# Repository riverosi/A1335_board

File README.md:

# A1335_board Project v1
Reposiorio de la pcb que usa el sensor [A1335](https://www.allegromicro.com/en/products/sense/linear-and-angular-position/angular-position-sensor-ics/a1335) de Allegro. Esta vesión tiene los siguientes requerimientos:
- [x] Los capacitores de desacople van a ir cerca del integrado
- [x] La mascara tendra una simbologia con la asigancion de pines
- [x] No se usaran las anotaciones en el cobre
- [x] Dimensiones propuestas: 50x40 mm
- [x] Se usaran pines como conectores
- [x] Tendrá 4 mountingholes tamaño M3
Vistas 3d del PCB:

# Montaje final del PCB con el Bumper:

## Firmware
En la carpeta firmware están los archivos `__angle_driver.h` y `__angle_driver.c`, que son los drivers en c para la plataforma de desarollo EDU-CIAA. En el main hay un ejemplo de como inicializar el dispositivo con las direcciones correspondientes al hardware que se desarrollo en la v1 (0x0C). 

## Software
Para desarrollar la placa se uso:
* [Doxygen](https://www.doxygen.nl/index.html) - To generate the documentation
* [VSCode](https://code.visualstudio.com/) - To communicate data through the UART (Developing)
* [KiCad](https://kicad.org/) - To develop de board

## Hardware
Para desarrollar la placa se uso **Kicad**, se debe de incluir la libraria HALL con el simbolo del componente A1335.

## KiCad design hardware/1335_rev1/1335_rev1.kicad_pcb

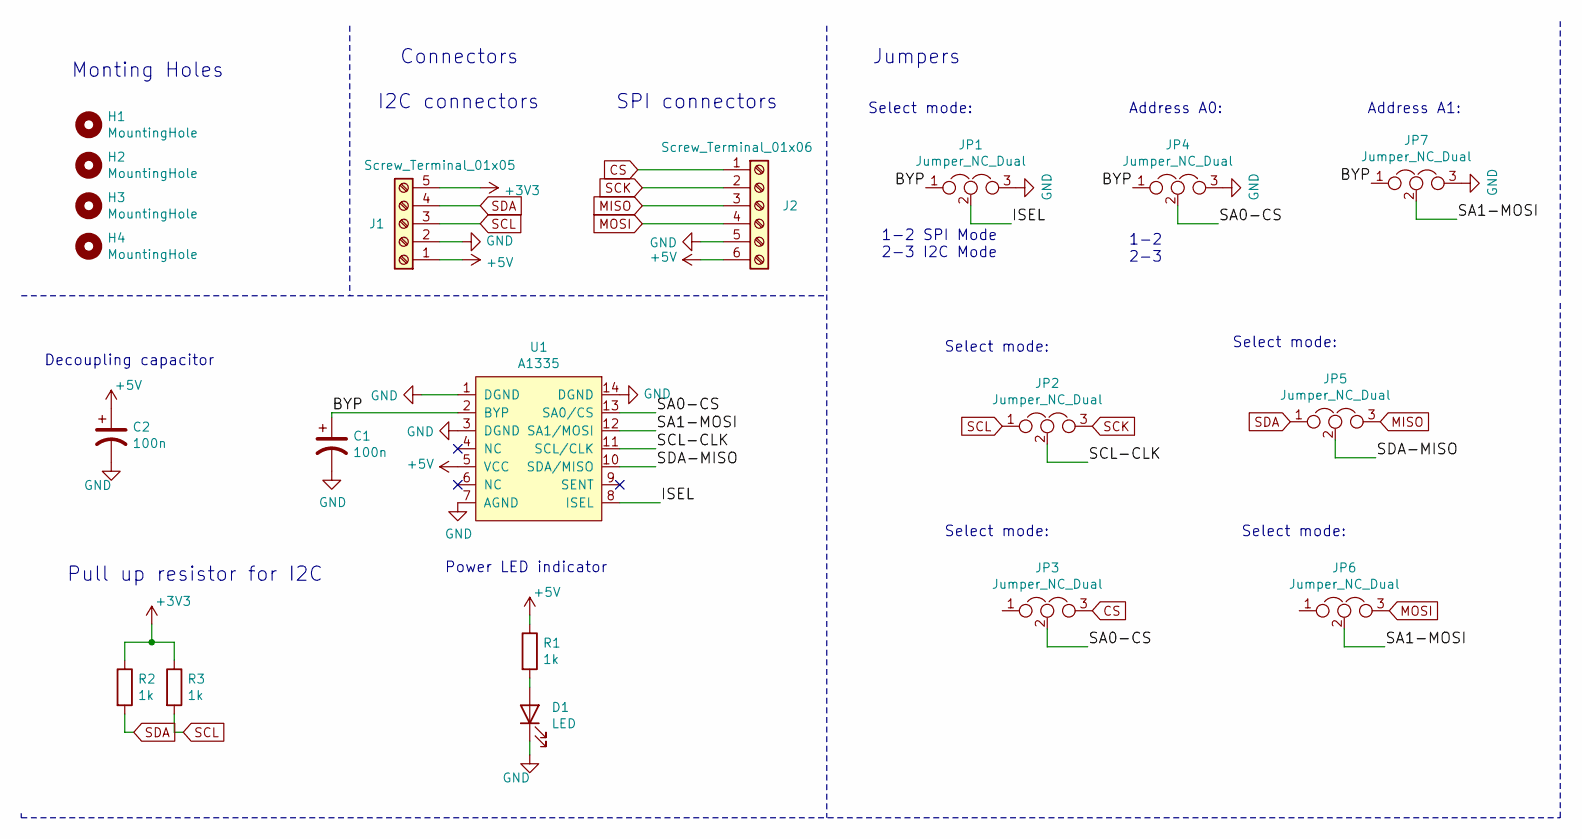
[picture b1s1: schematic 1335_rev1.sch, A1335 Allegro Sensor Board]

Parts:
C1, C2: 100n; CP_EIA-2012-15_AVX-P_Pad1.30x1.05mm_HandSolder
D1: LED; LED_0603_1608Metric
H1, H2, H3, H4: MountingHole; MountingHole_3.2mm_M3_Pad_Via
J1: Screw_Terminal_01x05; PinHeader_1x05_P2.54mm_Horizontal
J2: Screw_Terminal_01x06; PinHeader_1x06_P2.54mm_Horizontal
JP1, JP2, JP3, JP4, JP5, JP6, JP7: Jumper_NC_Dual; SolderJumper-3_P1.3mm_Open_RoundedPad1.0x1.5mm_NumberLabels
R1, R2, R3: 1k; R_0603_1608Metric
U1: A1335; TSSOP14

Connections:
+3V3: J1.5, R2.1, R3.1
+5V: C2.1, J1.1, J2.6, R1.1, U1.5 (VCC)
/BYP: C1.1, JP1.1, JP4.1, JP7.1, U1.2 (BYP)
/ISEL: JP1.2, U1.8 (ISEL)
/SA0-CS: JP3.2, JP4.2, U1.13 (SA0/CS)
/SA1-MOSI: JP6.2, JP7.2, U1.12 (SA1/MOSI)
/SCL-CLK: JP2.2, U1.11 (SCL/CLK)
/SDA-MISO: JP5.2, U1.10 (SDA/MISO)
CS: J2.1, JP3.3
GND: C1.2, C2.2, D1.1 (K), J1.2, J2.5, JP1.3, JP4.3, JP7.3, U1.1 (DGND), U1.3 (DGND), U1.7 (AGND), U1.14 (DGND)
MISO: J2.3, JP5.3
MOSI: J2.4, JP6.3
unnamed: D1.2 (A), R1.2
SCK: J2.2, JP2.3
SCL: J1.3, JP2.1, R3.2
SDA: J1.4, JP5.1, R2.2

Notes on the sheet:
Monting Holes
Jumpers
Select mode:
Connectors
Address A0:
Address A1:
Decoupling capacitor
I2C connectors
SPI connectors
1-2 SPI Mode 2-3 I2C Mode
1-2 2-3
Pull up resistor for I2C
Power LED indicator

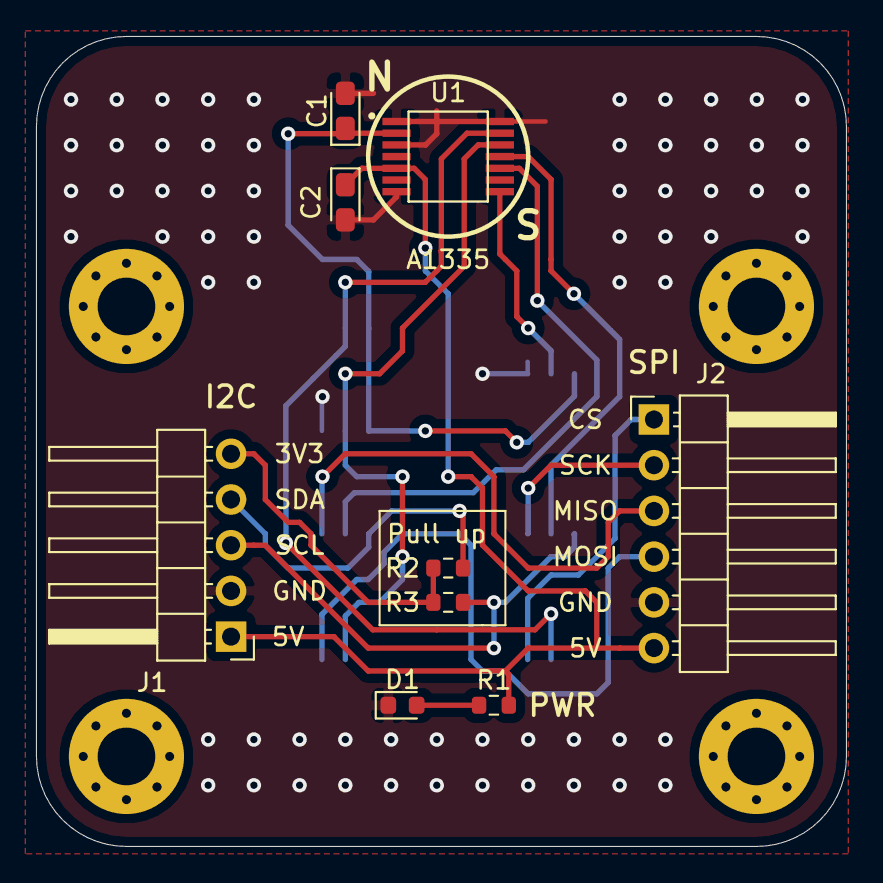
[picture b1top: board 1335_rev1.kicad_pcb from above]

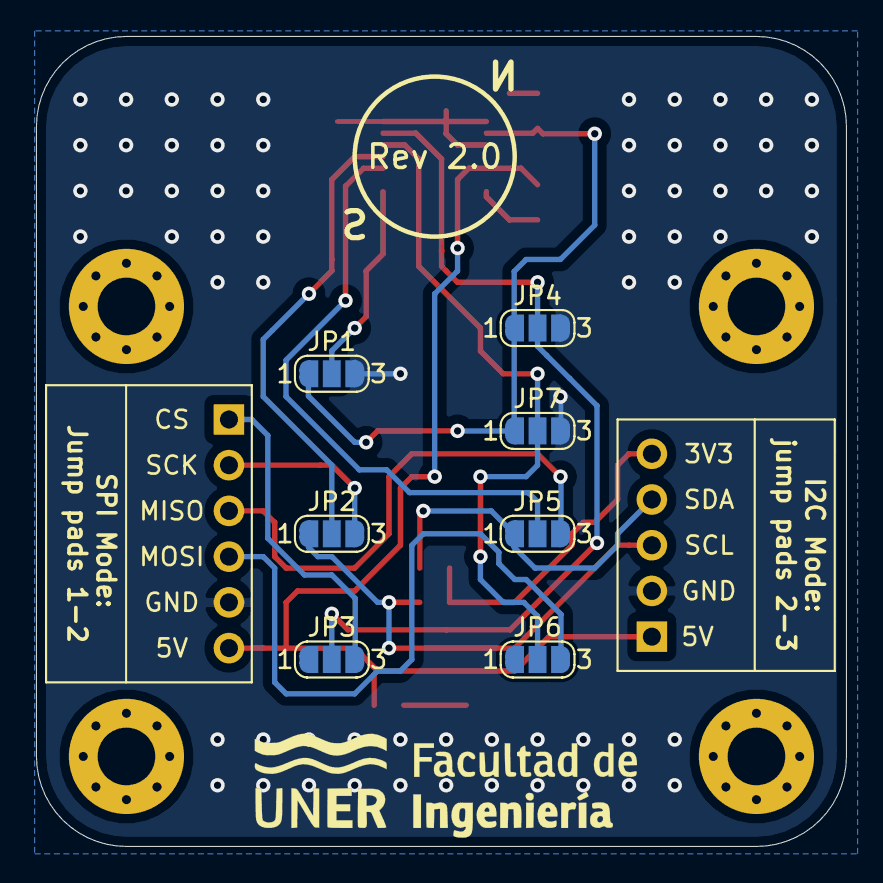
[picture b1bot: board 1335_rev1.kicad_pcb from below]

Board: 2 copper layers, 45.0 x 45.0 mm, 20 parts (7 on the bottom side), 16 nets.

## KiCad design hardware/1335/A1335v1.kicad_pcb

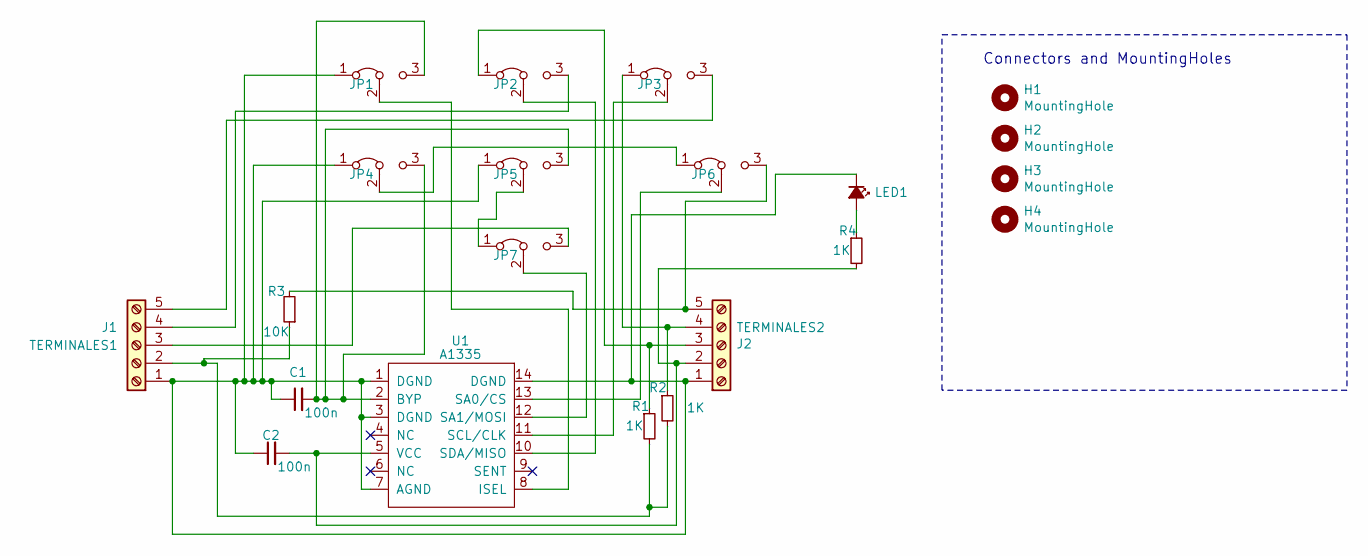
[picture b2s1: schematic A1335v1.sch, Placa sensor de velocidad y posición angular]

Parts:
C1, C2: 100n; CP_EIA-1608-08_AVX-J
H1, H2, H3, H4: MountingHole; MountingHole_3.2mm_M3_Pad_Via
J1: TERMINALES1; terminal_block_1x05_45DEG_3.81MM_5POS
J2: TERMINALES2; terminal_block_1x05_45DEG_3.81MM_5POS
JP1: 1; SolderJumper-3_P1.3mm_Bridged2Bar12_Pad1.0x1.5mm
JP2: 2; SolderJumper-3_P1.3mm_Bridged2Bar12_Pad1.0x1.5mm
JP3: 3; SolderJumper-3_P1.3mm_Bridged2Bar12_Pad1.0x1.5mm
JP4: 4; SolderJumper-3_P1.3mm_Bridged2Bar12_Pad1.0x1.5mm
JP5: 5; SolderJumper-3_P1.3mm_Bridged2Bar12_Pad1.0x1.5mm
JP6: 6; SolderJumper-3_P1.3mm_Bridged2Bar12_Pad1.0x1.5mm
JP7: 7; SolderJumper-3_P1.3mm_Bridged2Bar12_Pad1.0x1.5mm
LED1: LED; LED_0603_1608Metric
R1, R2, R4: 1K; R_0603_1608Metric
R3: 10K; R_0603_1608Metric
U1: A1335

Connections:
unnamed: C1.1, C2.1, J1.1, J2.1, JP1.1 (A), JP4.1 (A), JP5.1 (A), LED1.1 (K), U1.1 (DGND), U1.3 (DGND), U1.7 (AGND), U1.14 (DGND)
unnamed: C1.2, JP1.3 (B), JP4.3 (B), JP5.3 (B), U1.2 (BYP)
unnamed: C2.2, J2.2, R4.2, U1.5 (VCC)
unnamed: J1.2, R1.2, R2.2, R3.1
unnamed: J1.3, JP7.3 (B)
unnamed: J1.4, JP2.3 (B)
unnamed: J1.5, JP3.3 (B)
unnamed: J2.3, JP2.1 (A), R1.1
unnamed: J2.4, JP3.1 (A), R2.1
unnamed: J2.5, JP6.3 (B), R3.2
unnamed: JP1.2 (C), U1.8 (ISEL)
unnamed: JP2.2 (C), U1.10 (SDA/MISO)
unnamed: JP3.2 (C), U1.11 (SCL/CLK)
unnamed: JP4.2 (C), JP6.1 (A)
unnamed: JP5.2 (C), JP7.1 (A)
unnamed: JP6.2 (C), U1.13 (SA0/CS)
unnamed: JP7.2 (C), U1.12 (SA1/MOSI)
unnamed: LED1.2 (A), R4.1

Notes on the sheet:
Connectors and MountingHoles

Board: 2 copper layers, 20 parts (0 on the bottom side), 13 nets, no tracks yet.

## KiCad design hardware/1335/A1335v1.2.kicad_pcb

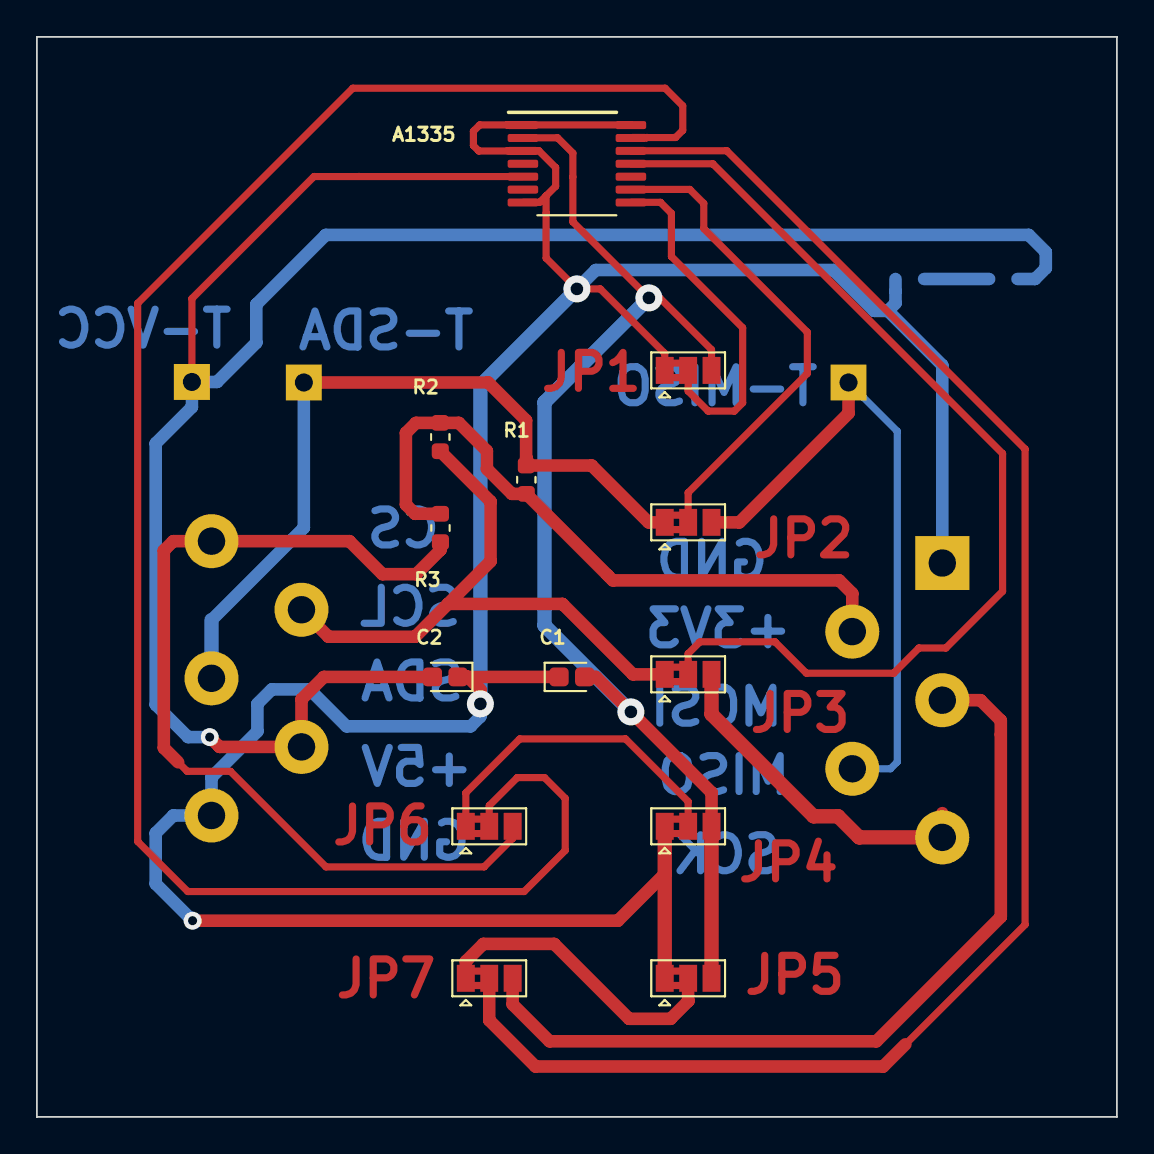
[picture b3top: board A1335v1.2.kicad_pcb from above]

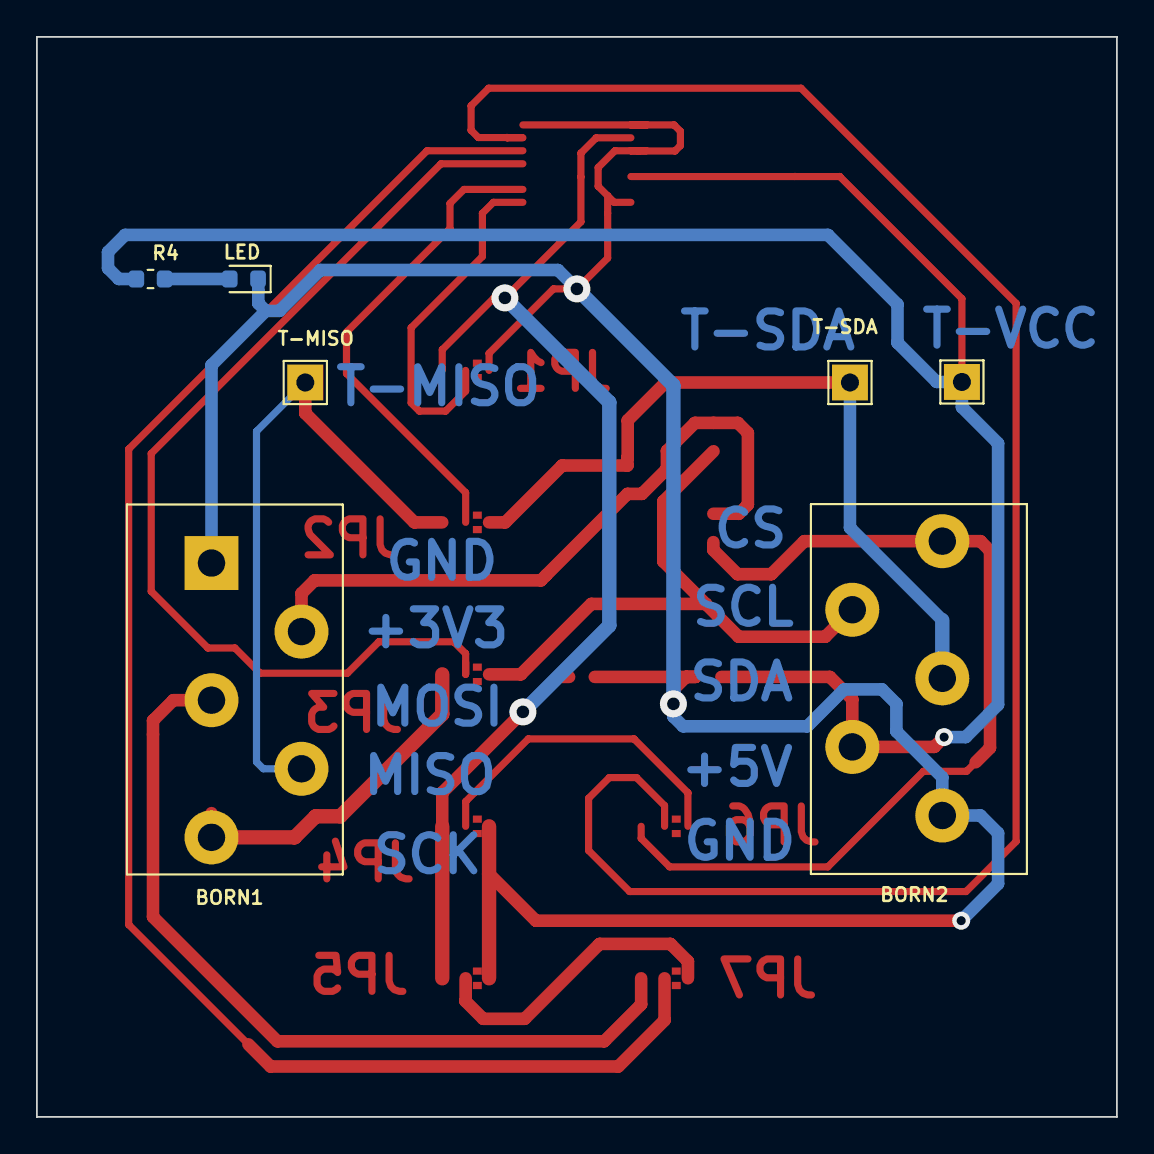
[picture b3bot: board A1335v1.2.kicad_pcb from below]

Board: 2 copper layers, 60.0 x 60.0 mm, 20 parts (7 on the bottom side), 18 nets.

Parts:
A1335: A1335
BORN1: TERMINALES1; terminalfes
BORN2: TERMINALES2; terminalfes
C1, C2: 100n; CP_EIA-1608-08_AVX-J
JP1: 1; SolderJumper-3_P1.3mm_Bridged2Bar12_Pad1.0x1.5mm
JP2: 2; SolderJumper-3_P1.3mm_Bridged2Bar12_Pad1.0x1.5mm
JP3: 3; SolderJumper-3_P1.3mm_Bridged2Bar12_Pad1.0x1.5mm
JP4: 4; SolderJumper-3_P1.3mm_Bridged2Bar12_Pad1.0x1.5mm
JP5: 5; SolderJumper-3_P1.3mm_Bridged2Bar12_Pad1.0x1.5mm
JP6: 6; SolderJumper-3_P1.3mm_Bridged2Bar12_Pad1.0x1.5mm
JP7: 7; SolderJumper-3_P1.3mm_Bridged2Bar12_Pad1.0x1.5mm
LED: LED; LED_0603_1608Metric
R1, R2, R4: 1K; R_0603_1608Metric
R3: 10K; R_0603_1608Metric
T-MISO: TP; TestPoint_THTPad_2.0x2.0mm_Drill1.0mm
T-SDA: TP; TestPoint_THTPad_2.0x2.0mm_Drill1.0mm
T-VCC: TP; TestPoint_THTPad_2.0x2.0mm_Drill1.0mm

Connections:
unnamed: A1335.1, A1335.3, A1335.7, A1335.14, BORN1.1, BORN2.1, C1.1, C2.1, JP1.1, JP4.1, JP5.1, LED.1
unnamed: A1335.2, C1.2, JP1.3, JP4.3, JP5.3
unnamed: A1335.5, BORN2.2, C2.2, R4.2, T-VCC.1
unnamed: BORN1.2, R1.2, R2.2, R3.1
unnamed: BORN1.3, JP7.3
unnamed: BORN1.4, JP2.3, T-MISO.1
unnamed: BORN1.5, JP3.3
unnamed: BORN2.3, JP2.1, R1.1, T-SDA.1
unnamed: BORN2.4, JP3.1, R2.1
unnamed: BORN2.5, JP6.3, R3.2
unnamed: A1335.8, JP1.2
unnamed: A1335.10, JP2.2
unnamed: A1335.11, JP3.2
unnamed: JP4.2, JP6.1
unnamed: JP5.2, JP7.1
unnamed: A1335.13, JP6.2
unnamed: A1335.12, JP7.2
unnamed: LED.2, R4.1

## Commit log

2021-02-18 Add files to project
2021-02-18 Add firmware
2021-02-18 Add doc
2021-03-01 Begin Revision of board
    Add mounting holes and changes in connectors
2021-03-08 add a1335_rev2 files
2021-03-10 Add 3d models, send to review pcb
2021-03-17 Add connectors and pull up resistors
2021-03-21 Add F.sliks anotations
2021-03-29 Updates in pcb
2021-04-13 Send to review
    Esteban Osella aprueba el diseño del PCB
2021-04-13 Add images to readme.md
2021-04-21 Change position of mh
2021-04-29 Generate gerber files
2021-05-28 Error in boom
2021-08-24 Add 3D bumper
2021-08-24 Add pic
2021-12-18 Add Schematic
